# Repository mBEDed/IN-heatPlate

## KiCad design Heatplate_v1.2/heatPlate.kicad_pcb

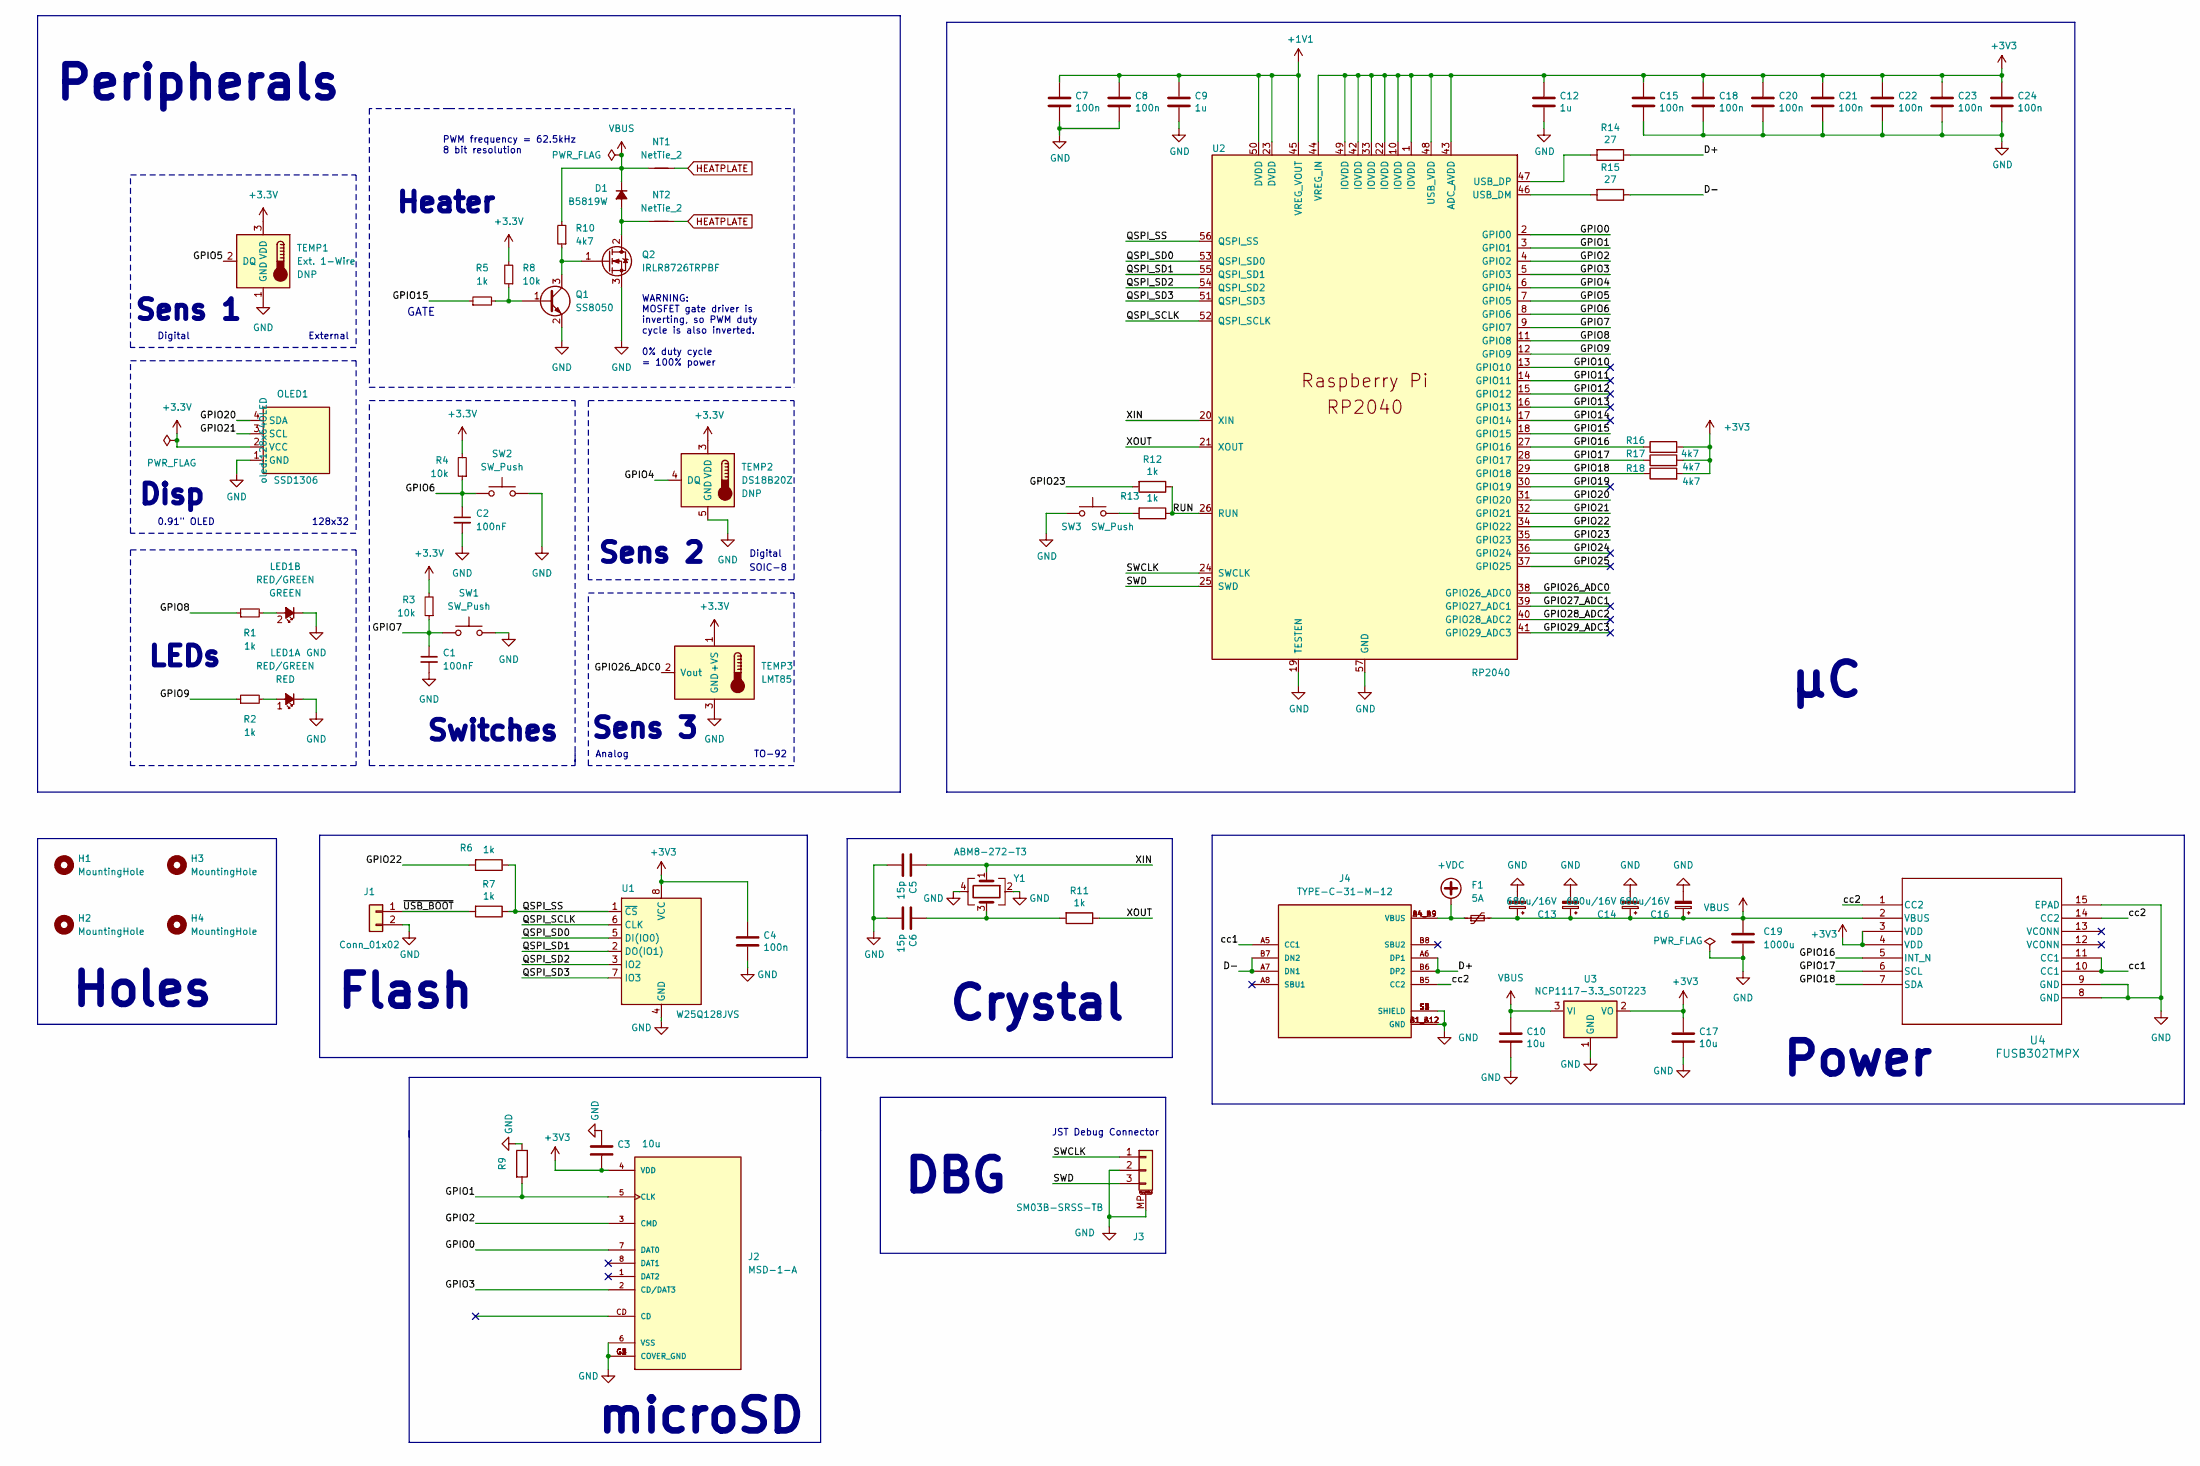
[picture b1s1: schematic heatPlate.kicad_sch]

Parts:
C1, C2: 100nF; C_0603_1608Metric; LCSC Part Number C1711
C3, C10, C17: 10u; C_0603_1608Metric
C4, C7, C8, C15, C18, C20, C21, C22, C23, C24: 100n; C_0603_1608Metric
C5, C6: 15p; C_0603_1608Metric
C9, C12: 1u; C_0603_1608Metric
C11, C13, C14, C16: 680u/16V; CP_Radial_D8.0mm_P3.50mm; LCSC Part Number C88760
C19: 1000u; C_0603_1608Metric
D1: B5819W; D_SOD-123; LCSC Part Number C64885
F1: 5A; Fuse_2920_7451Metric; LCSC Part Number C910846
H1, H2, H3, H4: MountingHole; MountingHole_2.2mm_M2
J1: Conn_01x02; PinHeader_1x02_P2.54mm_Vertical
J2: MSD-1-A; microSD_External_Pin; PARTREV 1.0
J3: SM03B-SRSS-TB; JST_SH_SM03B-SRSS-TB_1x03-1MP_P1.00mm_Horizontal
J4: TYPE-C-31-M-12; HRO_TYPE-C-31-M-12; PARTREV 2020.12.08
LED1: RED/GREEN; LED_Avago_PLCC4_3.2x2.8mm_CW; LCSC Part Number C131251
NT1, NT2: NetTie_2; NetTie-2_SMD_Pad0.5mm
OLED1: SSD1306; 128x64OLED; LCSC Part Number C2718488
Q1: SS8050; SOT-23; LCSC Part Number C444722
Q2: IRLR8726TRPBF; TO-252-2; LCSC Part Number C81137
R1, R2, R5: 1k; R_0603_1608Metric; LCSC Part Number C17513
R3, R4, R8: 10k; R_0603_1608Metric; LCSC Part Number C17414
R6, R7, R11, R12, R13: 1k; R_0603_1608Metric
R9: R_0603_1608Metric
R10: 4k7; R_0603_1608Metric; LCSC Part Number C17673
R14, R15: 27; R_0603_1608Metric
R16, R17, R18: 4k7; R_0603_1608Metric
SW1, SW2, SW3: SW_Push; SW_PUSH_6mm; LCSC Part Number C136682
TEMP1: Ext. 1-Wire; TO-92_Inline
TEMP2: DS18B20Z; SOIC-8_3.9x4.9mm_P1.27mm; LCSC Part Number C695837
TEMP3: LMT85; TO-92_Inline; LCSC Part Number C75856
U1: W25Q128JVS; SOIC-8_5.23x5.23mm_P1.27mm
U2: RP2040; RP2040-QFN-56
U3: NCP1117-3.3_SOT223; SOT-223-3_TabPin2
U4: FUSB302TMPX; WQFN14_2P5X2P5_ONS
Y1: ABM8-272-T3; Crystal_SMD_3225-4Pin_3.2x2.5mm

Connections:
+1V1: C7.1, C8.1, C9.1, U2.23 (DVDD), U2.45 (VREG_VOUT), U2.50 (DVDD)
+3.3V: OLED1.2 (VCC), R3.2, R4.2, R8.2, TEMP1.3 (VDD), TEMP2.3 (VDD), TEMP3.1 (+VS)
+3V3: C3.2, C4.1, C12.1, C15.1, C17.1, C18.1, C20.1, C21.1, C22.1, C23.1, C24.1, J2.4 (VDD), R16.2, R17.2, R18.2, U1.8 (VCC), U2.1 (IOVDD), U2.10 (IOVDD), U2.22 (IOVDD), U2.33 (IOVDD), U2.42 (IOVDD), U2.43 (ADC_AVDD), U2.44 (VREG_IN), U2.48 (USB_VDD), U2.49 (IOVDD), U3.2 (VO), U4.3 (VDD), U4.4 (VDD)
+VDC: F1.1, J4.A4_B9 (VBUS), J4.B4_A9 (VBUS)
/D+: J4.A6 (DP1), J4.B6 (DP2), R14.1
/D-: J4.A7 (DN1), J4.B7 (DN2), R15.1
/GPIO0: J2.7 (DAT0), U2.2 (GPIO0)
/GPIO1: J2.5 (CLK), R9.2, U2.3 (GPIO1)
/GPIO2: J2.3 (CMD), U2.4 (GPIO2)
/GPIO3: J2.2 (CD/DAT3), U2.5 (GPIO3)
/GPIO4: TEMP2.4 (DQ), U2.6 (GPIO4)
/GPIO5: TEMP1.2 (DQ), U2.7 (GPIO5)
/GPIO6: C2.1, R4.1, SW2.1, U2.8 (GPIO6)
/GPIO7: C1.1, R3.1, SW1.1, U2.9 (GPIO7)
/GPIO8: R1.1, U2.11 (GPIO8)
/GPIO9: R2.1, U2.12 (GPIO9)
/GPIO10: U2.13 (GPIO10)
/GPIO11: U2.14 (GPIO11)
/GPIO12: U2.15 (GPIO12)
/GPIO13: U2.16 (GPIO13)
/GPIO14: U2.17 (GPIO14)
/GPIO15: R5.1, U2.18 (GPIO15)
/GPIO16: R16.1, U2.27 (GPIO16), U4.5 (INT_N)
/GPIO17: R17.1, U2.28 (GPIO17), U4.6 (SCL)
/GPIO18: R18.1, U2.29 (GPIO18), U4.7 (SDA)
/GPIO19: U2.30 (GPIO19)
/GPIO20: OLED1.4 (SDA), U2.31 (GPIO20)
/GPIO21: OLED1.3 (SCL), U2.32 (GPIO21)
/GPIO22: R6.2, U2.34 (GPIO22)
/GPIO23: R12.2, U2.35 (GPIO23)
/GPIO24: U2.36 (GPIO24)
/GPIO25: U2.37 (GPIO25)
/GPIO26_ADC0: TEMP3.2 (Vout), U2.38 (GPIO26_ADC0)
/GPIO27_ADC1: U2.39 (GPIO27_ADC1)
/GPIO28_ADC2: U2.40 (GPIO28_ADC2)
/GPIO29_ADC3: U2.41 (GPIO29_ADC3)
/QSPI_SCLK: U1.6 (CLK), U2.52 (QSPI_SCLK)
/QSPI_SD0: U1.5 (DI(IO0)), U2.53 (QSPI_SD0)
/QSPI_SD1: U1.2 (DO(IO1)), U2.55 (QSPI_SD1)
/QSPI_SD2: U1.3 (IO2), U2.54 (QSPI_SD2)
/QSPI_SD3: U1.7 (IO3), U2.51 (QSPI_SD3)
/QSPI_SS: R6.1, R7.1, U1.1 (~CS), U2.56 (QSPI_SS)
/RUN: R12.1, R13.1, U2.26 (RUN)
/SWCLK: J3.1, U2.24 (SWCLK)
/SWD: J3.3, U2.25 (SWD)
/XIN: C5.1, U2.20 (XIN), Y1.1
/XOUT: R11.1, U2.21 (XOUT)
/cc1: J4.A5 (CC1), U4.10 (CC1), U4.11 (CC1)
/cc2: J4.B5 (CC2), U4.1 (CC2), U4.14 (CC2)
/~USB_BOOT: J1.1, R7.2
GND: C1.2, C2.2, C3.1, C4.2, C5.2, C6.2, C7.2, C8.2, C9.2, C10.2, C11.2, C12.2, C13.2, C14.2, C15.2, C16.2, C17.2, C18.2, C19.2, C20.2, C21.2, C22.2, C23.2, C24.2, J1.2, J2.6 (VSS), J2.G1 (COVER_GND), J2.G2 (COVER_GND), J2.G3 (COVER_GND), J2.G4 (COVER_GND), J3.2, J3.MP (MountPin), J4.A1_B12 (GND), J4.B1_A12 (GND), J4.S1 (SHIELD), J4.S2 (SHIELD), J4.S3 (SHIELD), J4.S4 (SHIELD), LED1.2 (K1), LED1.4 (K2), OLED1.1 (GND), Q1.2 (E), Q2.3 (S), R9.1, SW1.2, SW2.2, SW3.1, TEMP1.1 (GND), TEMP2.5 (GND), TEMP3.3 (GND), U1.4 (GND), U2.19 (TESTEN), U2.57 (GND), U3.1 (GND), U4.8 (GND), U4.9 (GND), U4.15 (EPAD), Y1.2, Y1.4
HEATPLATE: NT1.2, NT2.2
unnamed: C6.1, R11.2, Y1.3
unnamed: D1.2 (A), NT2.1, Q2.2 (D)
unnamed: LED1.1 (A1), R2.2
unnamed: LED1.3 (A2), R1.2
unnamed: Q1.1 (B), R5.2, R8.1
unnamed: Q1.3 (C), Q2.1 (G), R10.1
unnamed: R13.2, SW3.2
unnamed: R15.2, U2.46 (USB_DM)
unnamed: R14.2, U2.47 (USB_DP)
VBUS: C10.1, C11.1, C13.1, C14.1, C16.1, C19.1, D1.1 (K), F1.2, NT1.1, R10.2, U3.3 (VI), U4.2 (VBUS)

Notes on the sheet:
Digital
Crystal
DBG
Holes
Disp
0.91" OLED
Sens 2
TO-92
Sens 3
Sens 1
GATE
Analog
128x32
microSD
WARNING: MOSFET gate driver is inverting, so PWM duty cycle is also inverted. 0% duty cycle = 100% power
Switches
Peripherals
Power
JST Debug Connector
External
PWM frequency = 62.5kHz 8 bit resolution
Flash
SOIC-8
LEDs
Heater

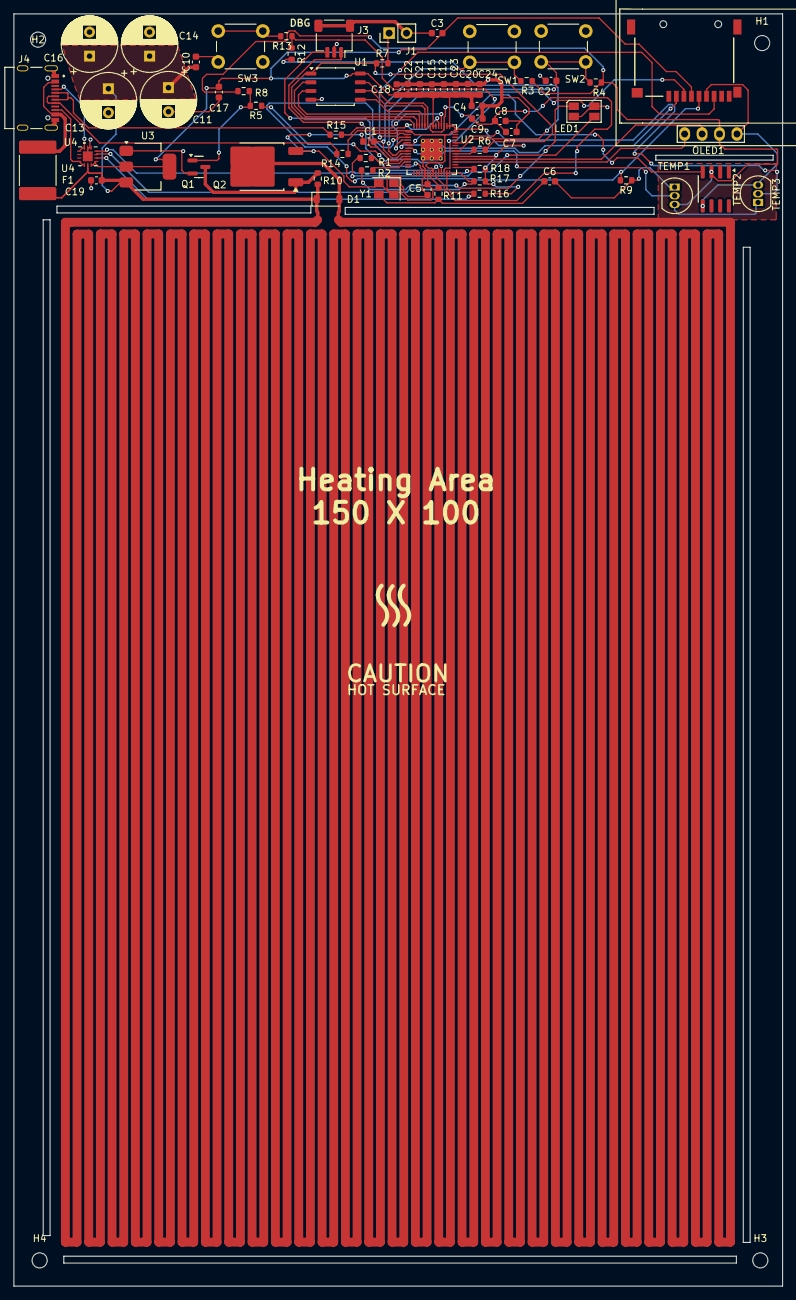
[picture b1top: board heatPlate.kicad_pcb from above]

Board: 2 copper layers, 112.0 x 185.4 mm, 69 parts (0 on the bottom side), 51 nets.

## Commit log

2024-12-24 Create temp
2025-01-02 First Update
2025-01-06 Heater dimension changed
2025-01-06 minor changes
2025-01-08 updated ignore
2025-01-15 updated cut-outs
2025-01-16 Minor placement changes
2025-01-16 components change to 0402
    compo
2025-01-16 components change to 0402
2025-01-16 components changed to 0603
2025-01-17 routing
2025-01-20 DRC Checked
2025-01-22 added dbg connector
2025-01-22 added reset switch
2025-01-22 sd-card added
2025-01-22 sd_card
2025-01-22 minor_changes
2025-01-24 minor changes
    fab outputs
2025-01-26 Add files via upload
    The `srpcode.ino` file serves as the main code for the Solder Reflow Plate project, designed to facilitate precise temperature control for soldering surface-mount devices (SMDs). It includes essentia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
2025-01-31 testCase
2025-02-03 test case
